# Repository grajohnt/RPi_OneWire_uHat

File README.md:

# Raspberry Pi OneWire uHat

This is a very simple uHat for the [Raspberry Pi Zero](https://www.raspberrypi.org/products/pi-zero/) sized uHat. It uses the [very nice template](https://github.com/mikelawrence/RPi_Zero_pHat_Template) from Mike Lawrence.

The purpose of this board is to simply allow connection of OneWire sensors (such as temperature sensors) that require a 4.7K pullup resistor. 

Connect up to four 5.08mm pitch terminal blocks. It should be possible to even put multiple sensors into the same terminal block.

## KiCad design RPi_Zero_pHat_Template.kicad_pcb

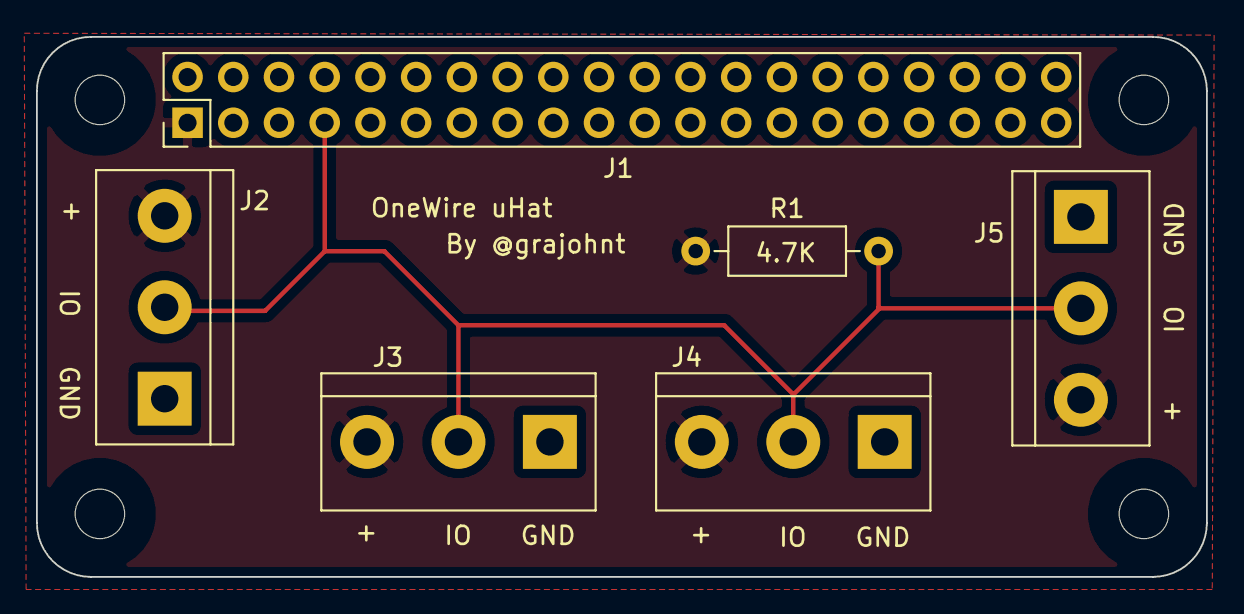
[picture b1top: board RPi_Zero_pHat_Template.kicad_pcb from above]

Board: 2 copper layers, 65.0 x 30.0 mm, 6 parts (0 on the bottom side), 3 nets.

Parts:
J1: RPi_GPIO; PinHeader_2x20_P2.54mm_Vertical
J2, J3, J4, J5: Screw_Terminal_01x03; TerminalBlock_bornier-3_P5.08mm
R1: 4.7K; R_Axial_DIN0207_L6.3mm_D2.5mm_P10.16mm_Horizontal

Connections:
/GND: J1.25, J2.1, J3.1, J4.1, J5.1
/IO: J1.7, J2.2, J3.2, J4.2, J5.2, R1.2
/V+: J1.1, J2.3, J3.3, J4.3, J5.3, R1.1

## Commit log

2020-06-23 Version 1.0 complete
